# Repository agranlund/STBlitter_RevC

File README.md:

<br>

<div align = center>

[![Badge License]][License]   
![Badge Revision]

<br>

# ST Blitter

A card providing **Blitter**, **IDE**, **TOS Decoding** as<br>
well as the **ET4000 Connector** for the **Atari ST(M)**.

***[Original][Anders Granlund Archive]*** *designed by* ***[Anders Granlund]***

<br>
<br>

[![Button Blitter]][Blitter]   
[![Button IDE]][IDE]   
[![Button TOS Decoding]][TOS Decoding]   
[![Button Graphics Card]][Graphics Card]

<br>
<br>

![Preview]

<br>
<br>

## Files

<br>

<table>
    <tr>
        <th>CPLD</th>
        <th>Eagle</th>
        <th colspan = '6'>Gerber</th>
    </tr>
    <tr>
        <td><a href = 'CPLD/STBLITTER_REVC_ATF1504.jed' ><b>JED</b></a></td>
        <td><a href = 'Eagle/STBlitter_RevC2.brd'       ><b>BRD</b></a></td>
        <td><a href = 'Gerber/STBlitter_RevC2.GBL'      ><b>GPL</b></a></td>
        <td><a href = 'Gerber/STBlitter_RevC2.GBP'      ><b>GBP</b></a></td>
        <td><a href = 'Gerber/STBlitter_RevC2.GL2'      ><b>GL2</b></a></td>
        <td><a href = 'Gerber/STBlitter_RevC2.GML'      ><b>GML</b></a></td>
        <td><a href = 'Gerber/STBlitter_RevC2.GTO'      ><b>GTO</b></a></td>
        <td><a href = 'Gerber/STBlitter_RevC2.GTS'      ><b>GTS</b></a></td>
    </tr>
    <tr>
        <td><a href = 'CPLD/STBLITTER_REVC_ATF1504.PLD' ><b>PLD</b></a></td>
        <td><a href = 'Eagle/STBlitter_RevC2.sch'       ><b>SCH</b></a></td>
        <td><a href = 'Gerber/STBlitter_RevC2.GBO'      ><b>GBO</b></a></td>
        <td><a href = 'Gerber/STBlitter_RevC2.GBS'      ><b>GBS</b></a></td>
        <td><a href = 'Gerber/STBlitter_RevC2.GL3'      ><b>GL3</b></a></td>
        <td><a href = 'Gerber/STBlitter_RevC2.GTL'      ><b>GTL</b></a></td>
        <td><a href = 'Gerber/STBlitter_RevC2.GTP'      ><b>GTP</b></a></td>
        <td><a href = 'Gerber/STBlitter_RevC2.TXT'      ><b>TXT</b></a></td>
    </tr>
</table>

<br>
<br>

## BOM

<br>

| Component | Value | Size |
|:----------|:-----:|:----:|
| **C**omplex <br> **P**rogrammable <br> **L**ogic <br> **D**evice | `ATF1504`
| **R1 , R2 , R5 , R6**      | `2.2㏀` | `0805`
| **R3 , R4 , R7 , R8 , R9** | `4.7㏀` | `0805`
| **Capacitors**             | `0.1㎌` | `0805`

</div>

<br>

<!----------------------------------------------------------------------------->

[Anders Granlund Archive]: https://web.archive.org/web/20211221080141/http://www.happydaze.se/
[Anders Granlund]: http://www.happydaze.se/

[Graphics Card]: Documentation/Graphics%20Card.md
[TOS Decoding]: Documentation/TOS%20Decoding.md
[Blitter]: Documentation/Blitter.md
[Preview]: Resources/Preview.png
[License]: LICENSE
[IDE]: Documentation/IDE.md

<!----------------------------------[ Badges ]--------------------------------->

[Badge Revision]: https://img.shields.io/badge/Revision-C2-7a1a43.svg?style=for-the-badge&labelColor=A9225C&logoColor=white&logo=GoogleAnalytics
[Badge License]: https://img.shields.io/badge/License-GPL2-015d93.svg?style=for-the-badge&labelColor=blue&logoColor=white&logo=GNU

<!---------------------------------[ Buttons ]--------------------------------->

[Button Graphics Card]: https://img.shields.io/badge/Graphics_Card-BA478F?style=for-the-badge&logoColor=white&logo=Polywork
[Button TOS Decoding]: https://img.shields.io/badge/TOS_Decoding-00A0DF?style=for-the-badge&logoColor=white&logo=PlayCanvas
[Button Blitter]: https://img.shields.io/badge/Blitter-E37400?style=for-the-badge&logoColor=white&logo=AmazonEC2
[Button IDE]: https://img.shields.io/badge/IDE-0C9D58?style=for-the-badge&logoColor=white&logo=GoogleSearchConsole

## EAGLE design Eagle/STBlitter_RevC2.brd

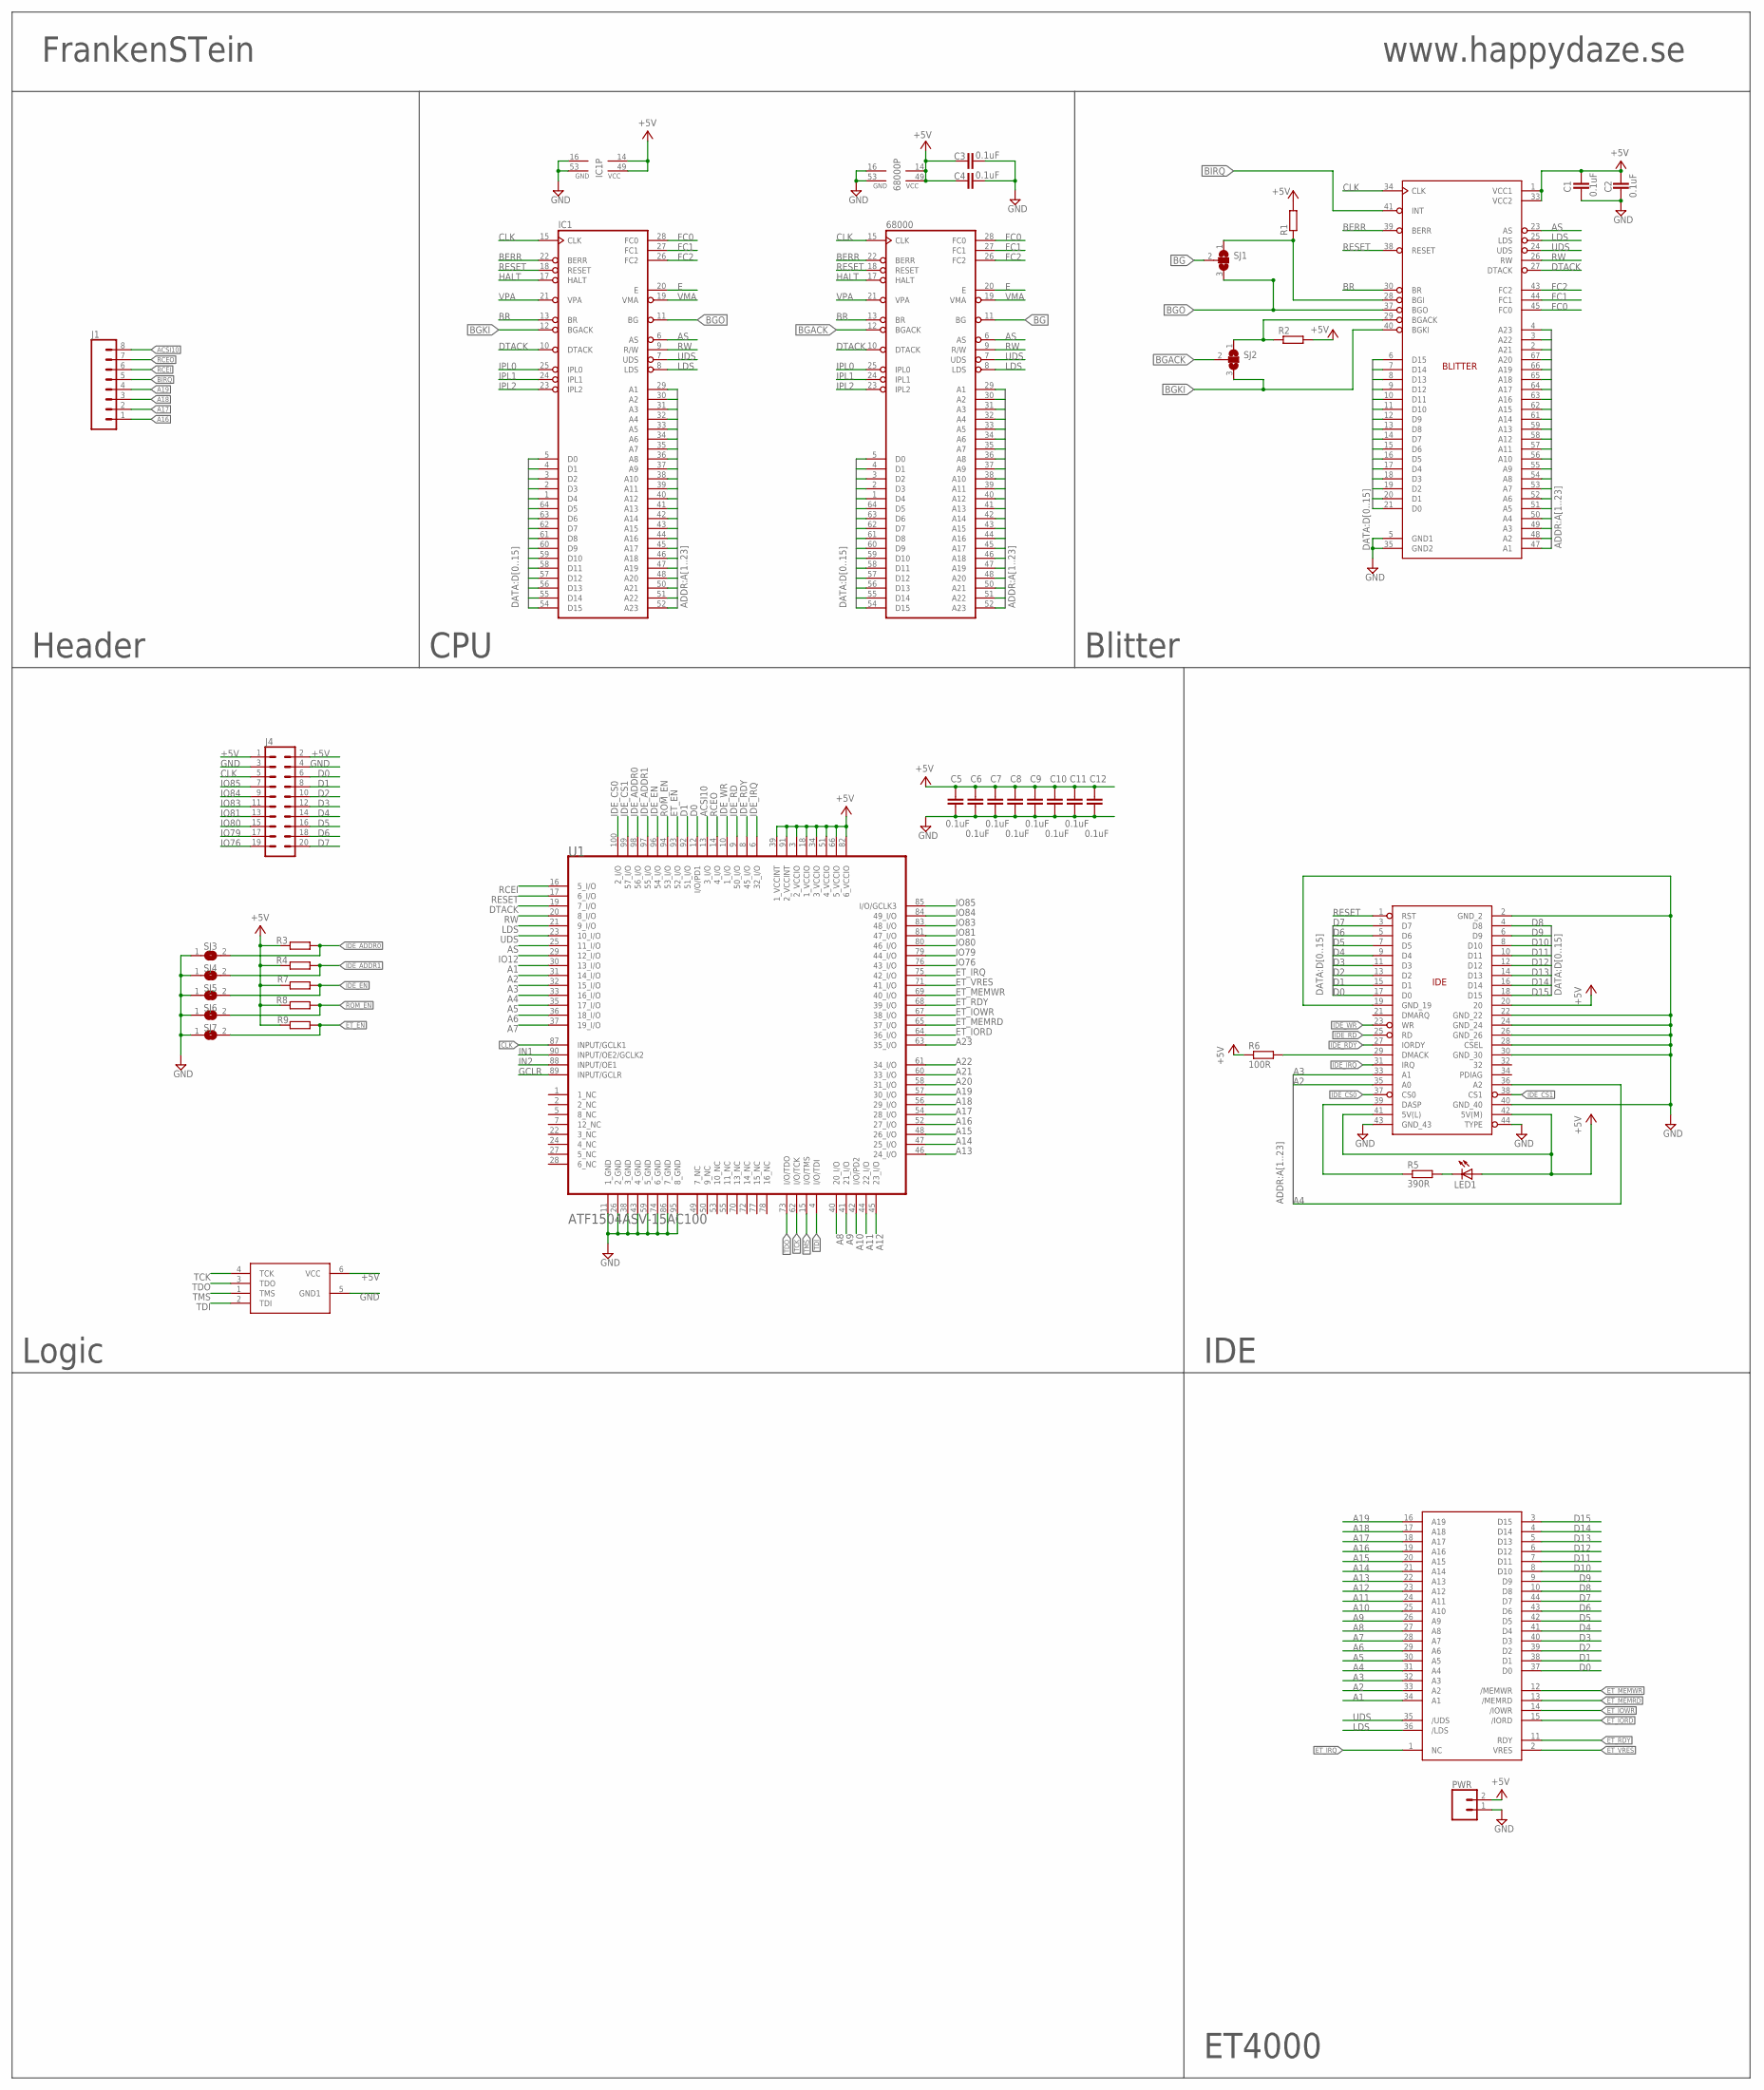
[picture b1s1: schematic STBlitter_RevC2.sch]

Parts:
68000: MC68000P; DIL64
BLITTER: STBLITTER; PLCC68-S
C1, C2, C3, C4, C5, C6, C7, C8, C9, C10, C11, C12: 0.1uF; C0805
CFCARD: IDE44_CON
IC1: MC68000P2; DIL64_SOCKET
J1: CONN_08"; 1X08
J4: CONN_10X2; 2X10
JTAG: JTAG_ATDH2
LED1: LED3MM
PWR: CONN_02; 1X02
R1, R2, R3, R4, R7, R8, R9: R-EU_R0805; R0805
R5: 390R; R0805
R6: 100R; R0805
SJ1, SJ2: SJ2W; SJ_2
SJ3, SJ4, SJ5, SJ6, SJ7: SJ
STGA: STGA; STGACON
U1: ATF1504_SMD100MICROCHIP_-_ATMEL_ATF1504ASV-15AC10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; MICROCHIP_-_ATMEL_ATF1504ASV-15AC100_1

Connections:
+5V: 68000.14 (VCC), 68000.49 (VCC), BLITTER.1 (VCC1), BLITTER.33 (VCC2), C1.1, C2.1, C3.1, C4.1, C5.2, C6.2, C7.2, C8.2, C9.2, C10.2, C11.2, C12.2, CFCARD.20, CFCARD.41 (5V(L)), CFCARD.42 (5V(M)), IC1.14 (VCC), IC1.49 (VCC), J4.1, J4.2, JTAG.6 (VCC), LED1.A, PWR.2, R1.2, R2.2, R3.1, R4.1, R6.1, R7.1, R8.1, R9.1, U1.3 (2_VCCIO), U1.18 (1_VCCIO), U1.34 (3_VCCIO), U1.39 (1_VCCINT), U1.51 (4_VCCIO), U1.66 (5_VCCIO), U1.82 (6_VCCIO), U1.91 (2_VCCINT)
A1: 68000.29 (A1), BLITTER.47 (A1), IC1.29 (A1), STGA.34 (A1), U1.30 (13_I/O)
A2: 68000.30 (A2), BLITTER.48 (A2), CFCARD.35 (A0), IC1.30 (A2), STGA.33 (A2), U1.31 (14_I/O)
A3: 68000.31 (A3), BLITTER.49 (A3), CFCARD.33 (A1), IC1.31 (A3), STGA.32 (A3), U1.32 (15_I/O)
A4: 68000.32 (A4), BLITTER.50 (A4), CFCARD.36 (A2), IC1.32 (A4), STGA.31 (A4), U1.33 (16_I/O)
A5: 68000.33 (A5), BLITTER.51 (A5), IC1.33 (A5), STGA.30 (A5), U1.35 (17_I/O)
A6: 68000.34 (A6), BLITTER.52 (A6), IC1.34 (A6), STGA.29 (A6), U1.36 (18_I/O)
A7: 68000.35 (A7), BLITTER.53 (A7), IC1.35 (A7), STGA.28 (A7), U1.37 (19_I/O)
A8: 68000.36 (A8), BLITTER.54 (A8), IC1.36 (A8), STGA.27 (A8), U1.40 (20_I/O)
A9: 68000.37 (A9), BLITTER.55 (A9), IC1.37 (A9), STGA.26 (A9), U1.41 (21_I/O)
A10: 68000.38 (A10), BLITTER.56 (A10), IC1.38 (A10), STGA.25 (A10), U1.42 (I/O/PD2)
A11: 68000.39 (A11), BLITTER.57 (A11), IC1.39 (A11), STGA.24 (A11), U1.44 (22_I/O)
A12: 68000.40 (A12), BLITTER.58 (A12), IC1.40 (A12), STGA.23 (A12), U1.45 (23_I/O)
A13: 68000.41 (A13), BLITTER.59 (A13), IC1.41 (A13), STGA.22 (A13), U1.46 (24_I/O)
A14: 68000.42 (A14), BLITTER.61 (A14), IC1.42 (A14), STGA.21 (A14), U1.47 (25_I/O)
A15: 68000.43 (A15), BLITTER.62 (A15), IC1.43 (A15), STGA.20 (A15), U1.48 (26_I/O)
A16: 68000.44 (A16), BLITTER.63 (A16), IC1.44 (A16), J1.1, STGA.19 (A16), U1.52 (27_I/O)
A17: 68000.45 (A17), BLITTER.64 (A17), IC1.45 (A17), J1.2, STGA.18 (A17), U1.54 (28_I/O)
A18: 68000.46 (A18), BLITTER.65 (A18), IC1.46 (A18), J1.3, STGA.17 (A18), U1.56 (29_I/O)
A19: 68000.47 (A19), BLITTER.66 (A19), IC1.47 (A19), J1.4, STGA.16 (A19), U1.57 (30_I/O)
A20: 68000.48 (A20), BLITTER.67 (A20), IC1.48 (A20), U1.58 (31_I/O)
A21: 68000.50 (A21), BLITTER.2 (A21), IC1.50 (A21), U1.60 (33_I/O)
A22: 68000.51 (A22), BLITTER.3 (A22), IC1.51 (A22), U1.61 (34_I/O)
A23: 68000.52 (A23), BLITTER.4 (A23), IC1.52 (A23), U1.63 (35_I/O)
ACSI10: J1.8, U1.13 (3_I/O)
AS: 68000.6 (AS), BLITTER.23 (AS), IC1.6 (AS), U1.25 (11_I/O)
BERR: 68000.22 (BERR), BLITTER.39 (BERR), IC1.22 (BERR)
BG: 68000.11 (BG), SJ1.2
BGACK: 68000.12 (BGACK), SJ2.2
BGKI: BLITTER.40 (BGKI), IC1.12 (BGACK), SJ2.3
BGO: BLITTER.37 (BGO), IC1.11 (BG), SJ1.3
BIRQ: BLITTER.41 (INT), J1.5
BLTBGI: BLITTER.28 (BGI), R1.1, SJ1.1
BR: 68000.13 (BR), BLITTER.30 (BR), IC1.13 (BR)
CLK: 68000.15 (CLK), BLITTER.34 (CLK), IC1.15 (CLK), J4.5, U1.87 (INPUT/GCLK1)
D0: 68000.5 (D0), BLITTER.21 (D0), CFCARD.17 (D0), IC1.5 (D0), J4.6, STGA.37 (D0), U1.12 (I/O/PD1)
D1: 68000.4 (D1), BLITTER.20 (D1), CFCARD.15 (D1), IC1.4 (D1), J4.8, STGA.38 (D1), U1.92 (51_I/O)
D2: 68000.3 (D2), BLITTER.19 (D2), CFCARD.13 (D2), IC1.3 (D2), J4.10, STGA.39 (D2)
D3: 68000.2 (D3), BLITTER.18 (D3), CFCARD.11 (D3), IC1.2 (D3), J4.12, STGA.40 (D3)
D4: 68000.1 (D4), BLITTER.17 (D4), CFCARD.9 (D4), IC1.1 (D4), J4.14, STGA.41 (D4)
D5: 68000.64 (D5), BLITTER.16 (D5), CFCARD.7 (D5), IC1.64 (D5), J4.16, STGA.42 (D5)
D6: 68000.63 (D6), BLITTER.15 (D6), CFCARD.5 (D6), IC1.63 (D6), J4.18, STGA.43 (D6)
D7: 68000.62 (D7), BLITTER.14 (D7), CFCARD.3 (D7), IC1.62 (D7), J4.20, STGA.44 (D7)
D8: 68000.61 (D8), BLITTER.13 (D8), CFCARD.4 (D8), IC1.61 (D8), STGA.10 (D8)
D9: 68000.60 (D9), BLITTER.12 (D9), CFCARD.6 (D9), IC1.60 (D9), STGA.9 (D9)
D10: 68000.59 (D10), BLITTER.11 (D10), CFCARD.8 (D10), IC1.59 (D10), STGA.8 (D10)
D11: 68000.58 (D11), BLITTER.10 (D11), CFCARD.10 (D11), IC1.58 (D11), STGA.7 (D11)
D12: 68000.57 (D12), BLITTER.9 (D12), CFCARD.12 (D12), IC1.57 (D12), STGA.6 (D12)
D13: 68000.56 (D13), BLITTER.8 (D13), CFCARD.14 (D13), IC1.56 (D13), STGA.5 (D13)
D14: 68000.55 (D14), BLITTER.7 (D14), CFCARD.16 (D14), IC1.55 (D14), STGA.4 (D14)
D15: 68000.54 (D15), BLITTER.6 (D15), CFCARD.18 (D15), IC1.54 (D15), STGA.3 (D15)
DASP: CFCARD.39 (DASP), R5.1
DMACK: CFCARD.29 (DMACK), R6.2
DTACK: 68000.10 (DTACK), BLITTER.27 (DTACK), IC1.10 (DTACK), U1.19 (7_I/O)
E: 68000.20 (E), IC1.20 (E)
ET_EN: R9.2, SJ7.2, U1.93 (52_I/O)
ET_IORD: STGA.15 (/IORD), U1.64 (36_I/O)
ET_IOWR: STGA.14 (/IOWR), U1.67 (38_I/O)
ET_IRQ: STGA.1 (NC), U1.75 (42_I/O)
ET_MEMRD: STGA.13 (/MEMRD), U1.65 (37_I/O)
ET_MEMWR: STGA.12 (/MEMWR), U1.69 (40_I/O)
ET_RDY: STGA.11 (RDY), U1.68 (39_I/O)
ET_VRES: STGA.2 (VRES), U1.71 (41_I/O)
FC0: 68000.28 (FC0), BLITTER.45 (FC0), IC1.28 (FC0)
FC1: 68000.27 (FC1), BLITTER.44 (FC1), IC1.27 (FC1)
FC2: 68000.26 (FC2), BLITTER.43 (FC2), IC1.26 (FC2)
GCLR: U1.89 (INPUT/GCLR)
GND: 68000.16 (GND), 68000.53 (GND), BLITTER.5 (GND1), BLITTER.35 (GND2), C1.2, C2.2, C3.2, C4.2, C5.1, C6.1, C7.1, C8.1, C9.1, C10.1, C11.1, C12.1, CFCARD.2 (GND_2), CFCARD.19 (GND_19), CFCARD.22 (GND_22), CFCARD.24 (GND_24), CFCARD.26 (GND_26), CFCARD.28 (CSEL), CFCARD.30 (GND_30), CFCARD.40 (GND_40), CFCARD.43 (GND_43), CFCARD.44 (TYPE), IC1.16 (GND), IC1.53 (GND), J4.3, J4.4, JTAG.5 (GND1), PWR.1, SJ3.1, SJ4.1, SJ5.1, SJ6.1, SJ7.1, U1.11 (1_GND), U1.26 (2_GND), U1.38 (3_GND), U1.43 (4_GND), U1.59 (5_GND), U1.74 (6_GND), U1.86 (7_GND), U1.95 (8_GND)
HALT: 68000.17 (HALT), IC1.17 (HALT)
IDE_ADDR0: R3.2, SJ3.2, U1.98 (56_I/O)
IDE_ADDR1: R4.2, SJ4.2, U1.97 (55_I/O)
IDE_CS0: CFCARD.37 (CS0), U1.100 (2_I/O)
IDE_CS1: CFCARD.38 (CS1), U1.99 (57_I/O)
IDE_EN: R7.2, SJ5.2, U1.96 (54_I/O)
IDE_IRQ: CFCARD.31 (IRQ), U1.6 (32_I/O)
IDE_RD: CFCARD.25 (RD), U1.9 (50_I/O)
IDE_RDY: CFCARD.27 (IORDY), U1.8 (45_I/O)
IDE_WR: CFCARD.23 (WR), U1.10 (1_I/O)
IN1: U1.90 (INPUT/OE2/GCLK2)
IN2: U1.88 (INPUT/OE1)
IO12: U1.29 (12_I/O)
IO76: J4.19, U1.76 (43_I/O)
IO79: J4.17, U1.79 (44_I/O)
IO80: J4.15, U1.80 (46_I/O)
IO81: J4.13, U1.81 (47_I/O)
IO83: J4.11, U1.83 (48_I/O)
IO84: J4.9, U1.84 (49_I/O)
IO85: J4.7, U1.85 (I/O/GCLK3)
IPL0: 68000.25 (IPL0), IC1.25 (IPL0)
IPL1: 68000.24 (IPL1), IC1.24 (IPL1)
IPL2: 68000.23 (IPL2), IC1.23 (IPL2)
LDS: 68000.8 (LDS), BLITTER.25 (LDS), IC1.8 (LDS), STGA.36 (/LDS), U1.21 (9_I/O)
unnamed: LED1.K (C), R5.2
RCEI: J1.6, U1.16 (5_I/O)
RCEO: J1.7, U1.14 (4_I/O)
RESET: 68000.18 (RESET), BLITTER.38 (RESET), CFCARD.1 (RST), IC1.18 (RESET), U1.17 (6_I/O)
ROM_EN: R8.2, SJ6.2, U1.94 (53_I/O)
RW: 68000.9 (R/W), BLITTER.26 (RW), IC1.9 (R/W), U1.20 (8_I/O)
TCK: JTAG.4 (TCK), U1.62 (I/O/TCK)
TDI: JTAG.2 (TDI), U1.4 (I/O/TDI)
TDO: JTAG.3 (TDO), U1.73 (I/O/TDO)
TMS: JTAG.1 (TMS), U1.15 (I/O/TMS)
UDS: 68000.7 (UDS), BLITTER.24 (UDS), IC1.7 (UDS), STGA.35 (/UDS), U1.23 (10_I/O)
VMA: 68000.19 (VMA), IC1.19 (VMA)
VPA: 68000.21 (VPA), IC1.21 (VPA)
_BGACK: BLITTER.29 (BGACK), R2.1, SJ2.1

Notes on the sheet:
FrankenSTein
www.happydaze.se
Blitter
IDE
Logic
Header
CPU
ET4000

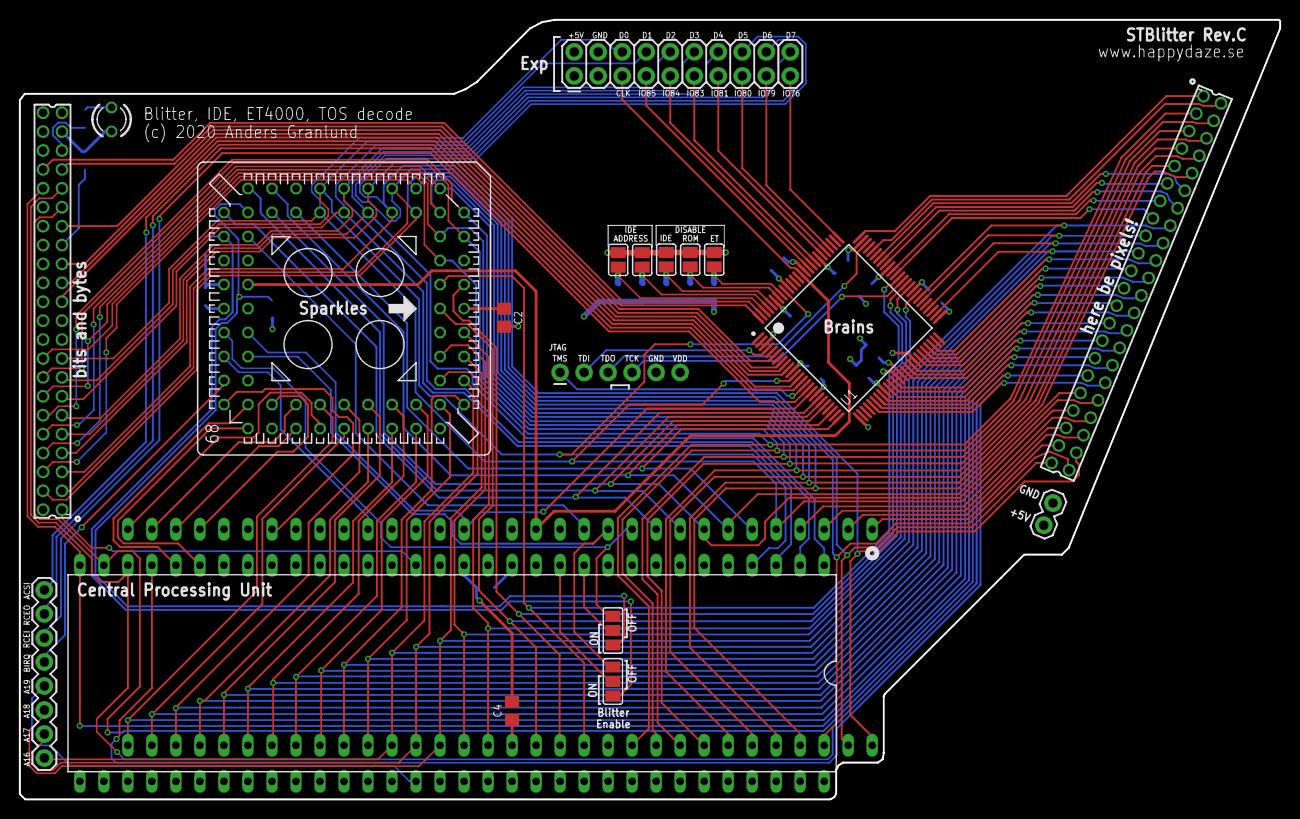
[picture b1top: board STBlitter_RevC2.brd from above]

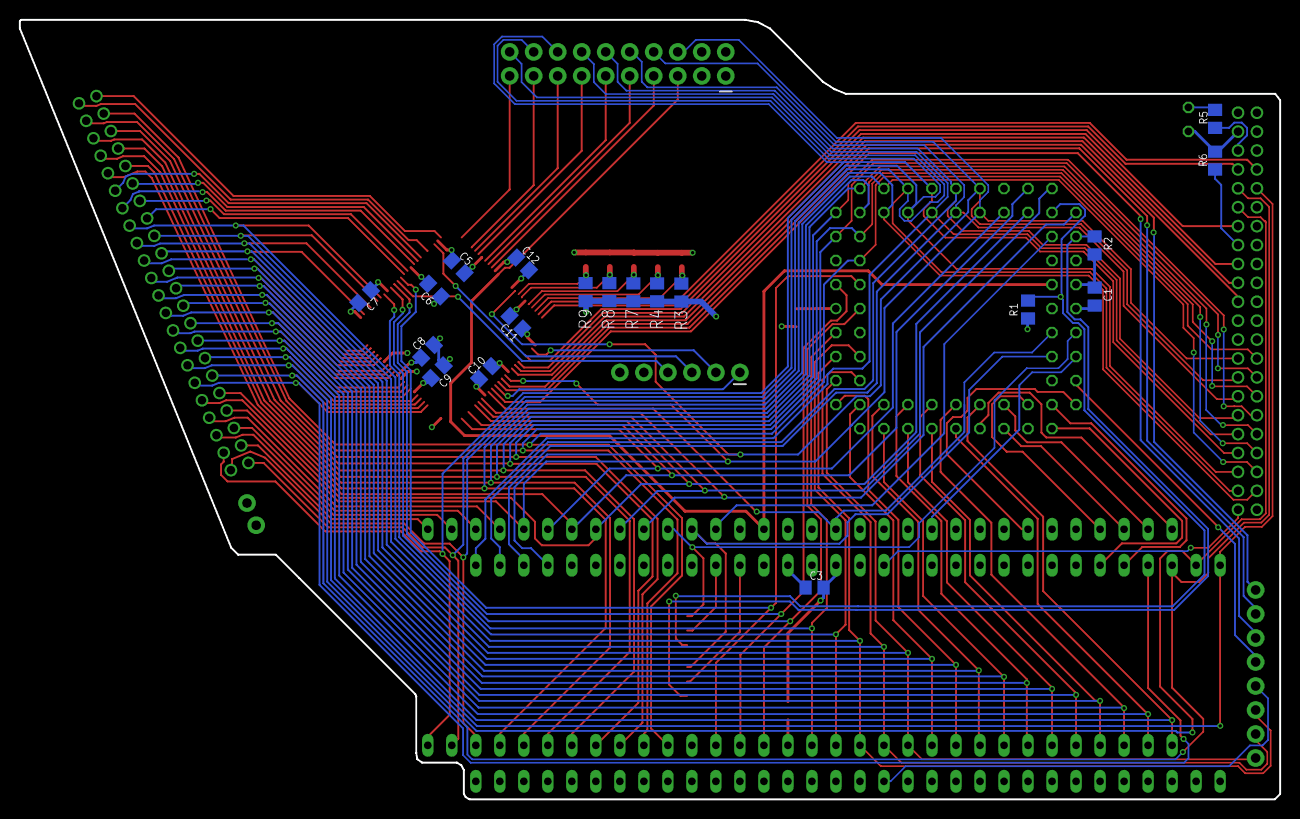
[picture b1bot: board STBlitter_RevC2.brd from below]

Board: 4 copper layers, 133.3 x 82.5 mm, 39 parts (19 on the bottom side), 102 nets.

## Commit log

2020-12-01 et4000 tweaks
2020-12-01 Improved ET4000 readback timing
2021-12-21 Repo Refactor
2022-08-02 Split Up Topics
2022-08-02 Formatted README
2022-08-02 Adjusted Formatting

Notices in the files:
Eagle/STBlitter_RevC2.brd:
(c) 2020 Anders Granlund
parts and their libraries:
SparkFun-Connectors: Licensing: Creative Commons ShareAlike 4.0 International - https://creativecommons.org/licenses/by-sa/4.0
